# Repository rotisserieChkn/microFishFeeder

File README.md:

## About

WORK IN PROGRESS

## Licensing

This repository contains hardware and firmware components
that are licensed separately.

### Hardware and Mechanical

All original hardware design files in the `hardware/` and `mechanical/`
directory are licensed under the CERN Open Hardware
License Version 2 - Weakly Reciprocal (CERN-OHL-W-2.0).

### Firmware

All original firmware source code in the `firmware/`
directory is licensed under the Mozilla Public License
2.0 (MPL-2.0).

### Third-party components

Third-party components retain their respective original
licenses. See their accompanying license notices where
applicable.

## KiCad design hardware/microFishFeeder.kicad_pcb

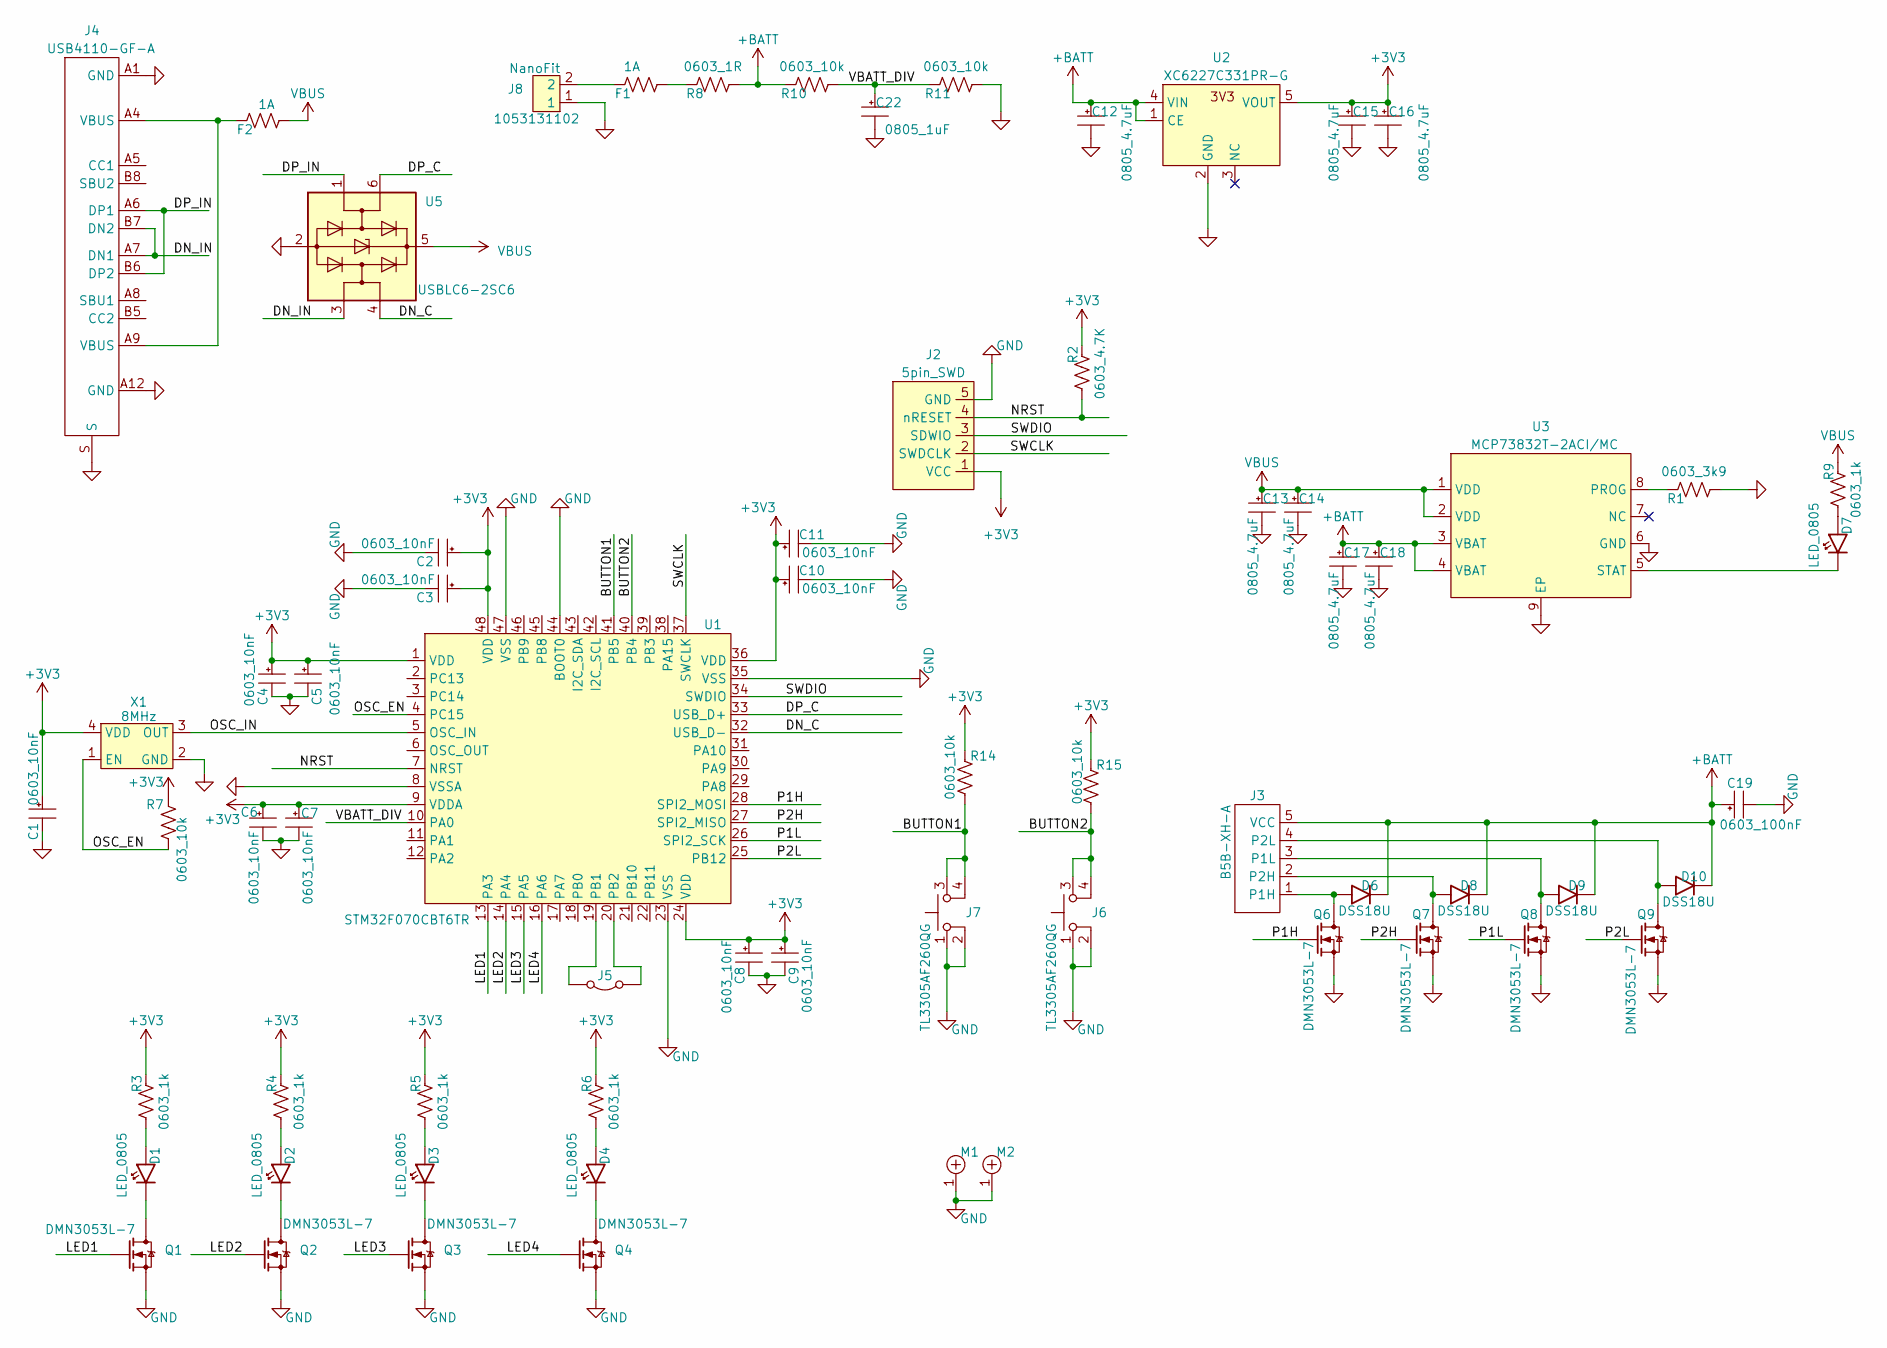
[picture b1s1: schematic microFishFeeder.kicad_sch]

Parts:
C1, C2, C3, C4, C5, C6, C7, C8, C9, C10, C11: 0603_10nF; C_0603_1608Metric
C12, C13, C14, C15, C16, C17, C18: 0805_4.7uF; C_0805_2012Metric
C19: 0603_100nF; C_0603_1608Metric
C22: 0805_1uF; C_0805_2012Metric
D1, D2, D3, D4, D7: LED_0805; R_0805_2012Metric
D6, D8, D9, D10: DSS18U; D_SOD-123F; MFG_PN DSS18U
F1, F2: 1A; R_0603_1608Metric; MFG_PN 0467001.NRHF
J2: 5pin_SWD; PinHeader_1x05_P2.54mm_Vertical
J3: B5B-XH-A(LF)(SN); MFG_PN B5B-XH-A
J4: USB4110-GF-A; MFG_PN USB4110-GF-A
J5: jumper_header; PinHeader_1x02_P2.54mm_Vertical
J6, J7: TL3305AF260QG; MFG_PN TL3305AF260QG
J8: NanoFit; nanofit_1053131102; MFG_PN 1053131102
M1, M2: mech_3.5mm
Q1, Q2, Q3, Q4, Q6, Q7, Q8, Q9: SOT-23-3; MFG_PN DMN3053L-7
R1: 0603_3k9; R_0603_1608Metric
R2: 0603_4.7K; R_0603_1608Metric
R3, R4, R5, R6, R9: 0603_1k; R_0603_1608Metric
R7, R10, R11, R14, R15: 0603_10k; R_0603_1608Metric
R8: 0603_1R; R_0603_1608Metric
U1: STM32F070CBT6TR; MFG_PN STM32F070CBT6TR
U2: XC6227C331PR-G; SOT-89-5; MFG_PN XC6227C331PR-G
U3: MCP73832T-2ACI/MC; MCP73832T; MFG_PN MCP73832T-2ACI/MC
U5: USBLC6-2SC6; SOT-23-6; MFG_PN USBLC6-2SC6
X1: 8MHz; 50_MHz_OSC; MFG_PN ECS-2520MVLC-080-CN-TR

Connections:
+3V3: C1.1, C2.1, C3.1, C4.1, C5.1, C6.1, C7.1, C8.1, C9.1, C10.1, C11.1, C15.1, C16.1, J2.1 (VCC), R2.2, R3.2, R4.2, R5.2, R6.2, R7.1, R14.2, R15.2, U1.1 (VDD), U1.9 (VDDA), U1.24 (VDD), U1.36 (VDD), U1.48 (VDD), U2.5 (VOUT), X1.4 (VDD)
+BATT: C12.1, C17.1, C18.1, C19.1, D6.1, D8.1, D9.1, D10.1, J3.5 (VCC), R8.1, R10.2, U2.1 (CE), U2.4 (VIN), U3.3 (VBAT), U3.4 (VBAT)
/BUTTON1: J7.3, J7.4, R14.1, U1.41 (PB5)
/BUTTON2: J6.3, J6.4, R15.1, U1.40 (PB4)
/DN_C: U1.32 (USB_D-), U5.4 (I/O2)
/DN_IN: J4.A7 (DN1), J4.B7 (DN2), U5.3 (I/O2)
/DP_C: U1.33 (USB_D+), U5.6 (I/O1)
/DP_IN: J4.A6 (DP1), J4.B6 (DP2), U5.1 (I/O1)
/LED1: Q1.1 (G), U1.13 (PA3)
/LED2: Q2.1 (G), U1.14 (PA4)
/LED3: Q3.1 (G), U1.15 (PA5)
/LED4: Q4.1 (G), U1.16 (PA6)
/NRST: J2.4 (nRESET), R2.1, U1.7 (NRST)
/OSC_EN: R7.2, U1.4 (PC15), X1.1 (EN)
/OSC_IN: U1.5 (OSC_IN), X1.3 (OUT)
/P1H: Q6.1 (G), U1.28 (SPI2_MOSI)
/P1L: Q8.1 (G), U1.26 (SPI2_SCK)
/P2H: Q7.1 (G), U1.27 (SPI2_MISO)
/P2L: Q9.1 (G), U1.25 (PB12)
/SWCLK: J2.2 (SWDCLK), U1.37 (SWCLK)
/SWDIO: J2.3 (SDWIO), U1.34 (SWDIO)
/VBATT_DIV: C22.1, R10.1, R11.2, U1.10 (PA0)
GND: C1.2, C2.2, C3.2, C4.2, C5.2, C6.2, C7.2, C8.2, C9.2, C10.2, C11.2, C12.2, C13.2, C14.2, C15.2, C16.2, C17.2, C18.2, C19.2, C22.2, J2.5 (GND), J4.A1 (GND), J4.A12 (GND), J4.S, J6.1, J6.2, J7.1, J7.2, J8.1, M1.1, M2.1, Q1.2 (S), Q2.2 (S), Q3.2 (S), Q4.2 (S), Q6.2 (S), Q7.2 (S), Q8.2 (S), Q9.2 (S), R1.1, R11.1, U1.8 (VSSA), U1.23 (VSS), U1.35 (VSS), U1.44 (BOOT0), U1.47 (VSS), U2.2 (GND), U3.6 (GND), U3.9 (EP), U5.2 (GND), X1.2 (GND)
unnamed: D1.2, R3.1
unnamed: D2.2, R4.1
unnamed: D3.2, R5.1
unnamed: D4.2, R6.1
unnamed: D7.2, R9.1
unnamed: F1.1, R8.2
unnamed: F1.2, J8.2
unnamed: F2.2, J4.A4 (VBUS), J4.A9 (VBUS)
unnamed: D6.2, J3.1 (P1H), Q6.3 (D)
unnamed: D9.2, J3.3 (P1L), Q8.3 (D)
unnamed: D8.2, J3.2 (P2H), Q7.3 (D)
unnamed: D10.2, J3.4 (P2L), Q9.3 (D)
unnamed: J5.1 (A), U1.20 (PB2)
unnamed: J5.2 (B), U1.19 (PB1)
unnamed: D1.1, Q1.3 (D)
unnamed: D2.1, Q2.3 (D)
unnamed: D3.1, Q3.3 (D)
unnamed: D4.1, Q4.3 (D)
unnamed: R1.2, U3.8 (PROG)
unnamed: D7.1, U3.5 (STAT)
VBUS: C13.1, C14.1, F2.1, R9.2, U3.1 (VDD), U3.2 (VDD), U5.5 (VBUS)

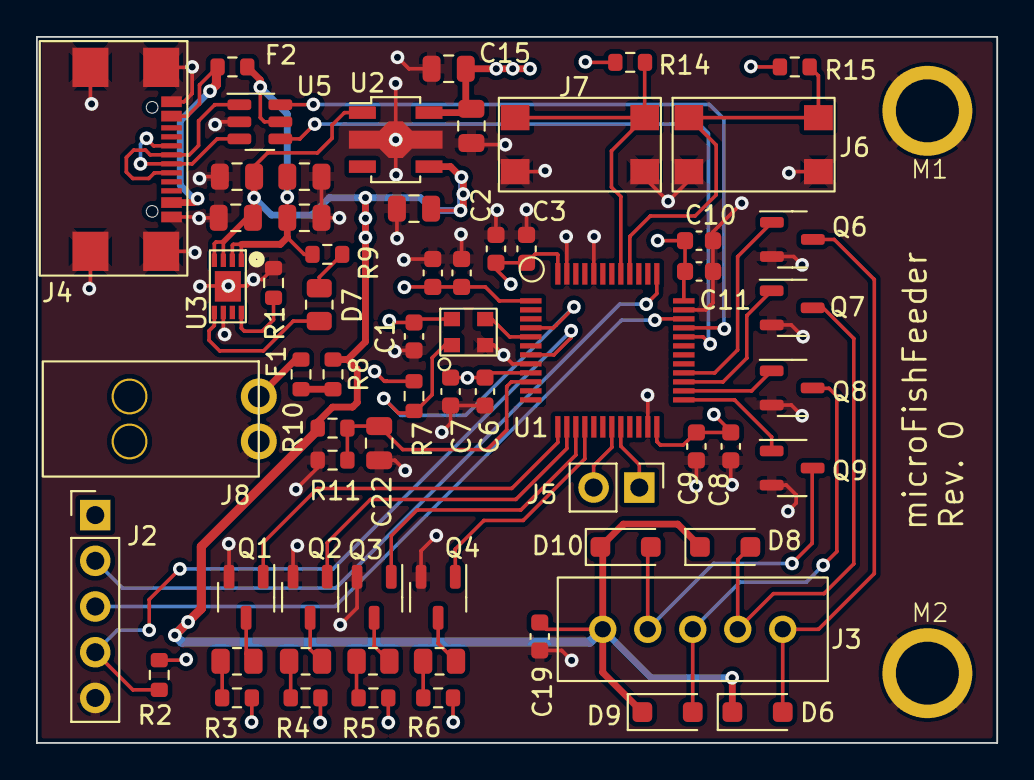
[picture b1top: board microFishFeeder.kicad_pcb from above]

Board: 4 copper layers, 53.3 x 39.2 mm, 66 parts (0 on the bottom side), 44 nets.
